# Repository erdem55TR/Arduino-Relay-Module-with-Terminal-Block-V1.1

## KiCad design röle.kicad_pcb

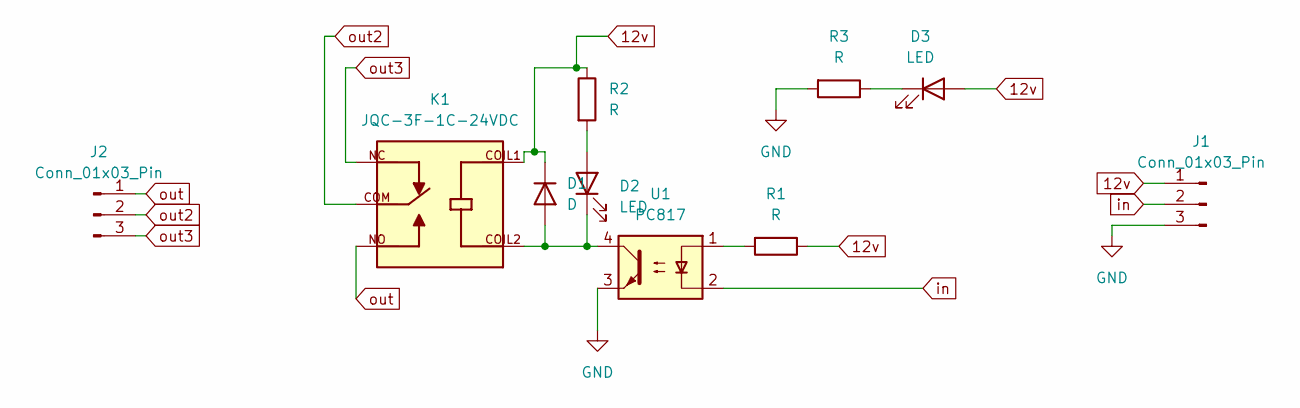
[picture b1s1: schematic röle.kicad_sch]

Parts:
D1: D; D_5W_P10.16mm_Horizontal
D2, D3: LED; LED_D5.0mm_Clear
J1, J2: Conn_01x03_Pin; PhoenixContact_MCV_1,5_3-G-5.08_1x03_P5.08mm_Vertical
K1: JQC-3F-1C-24VDC; RELAY_JQC-3F-1C-24VDC; PARTREV N/A
R1, R2, R3: R; R_Axial_DIN0207_L6.3mm_D2.5mm_P10.16mm_Horizontal
U1: PC817; DIP-4_W7.62mm

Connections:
12v: D1.1 (K), D3.2 (A), J1.1, K1.COIL1, R1.1, R2.1
GND: J1.3, R3.2, U1.3
unnamed: D1.2 (A), D2.1 (K), K1.COIL2, U1.4
unnamed: D2.2 (A), R2.2
unnamed: D3.1 (K), R3.1
unnamed: R1.2, U1.1
in: J1.2, U1.2
out: J2.1, K1.NO
out2: J2.2, K1.COM
out3: J2.3, K1.NC

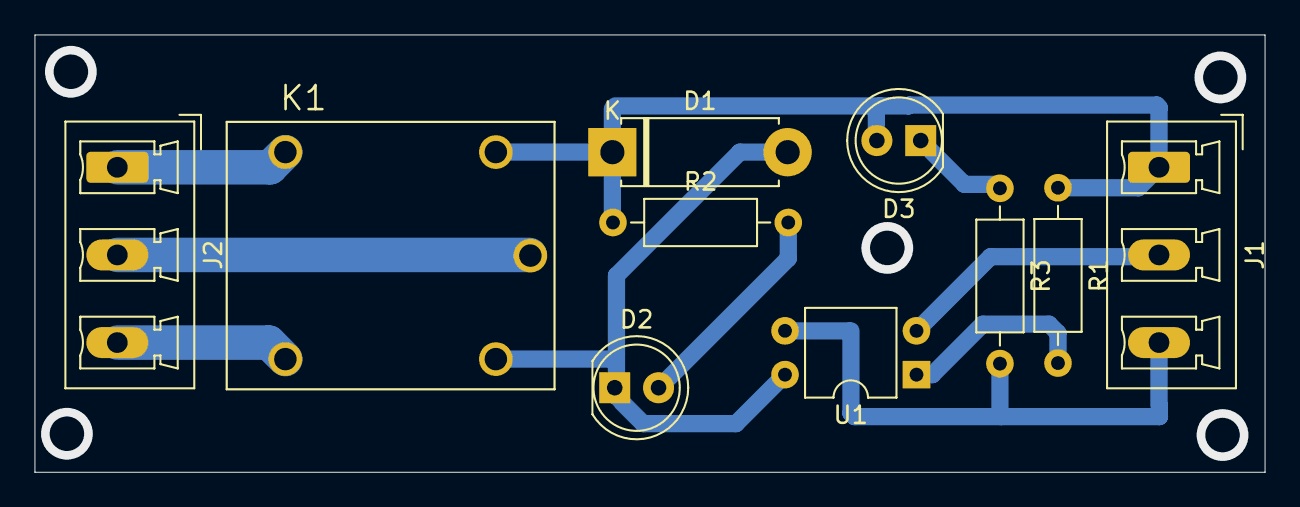
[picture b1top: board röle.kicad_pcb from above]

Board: 2 copper layers, 71.3 x 25.3 mm, 10 parts (0 on the bottom side), 10 nets.
